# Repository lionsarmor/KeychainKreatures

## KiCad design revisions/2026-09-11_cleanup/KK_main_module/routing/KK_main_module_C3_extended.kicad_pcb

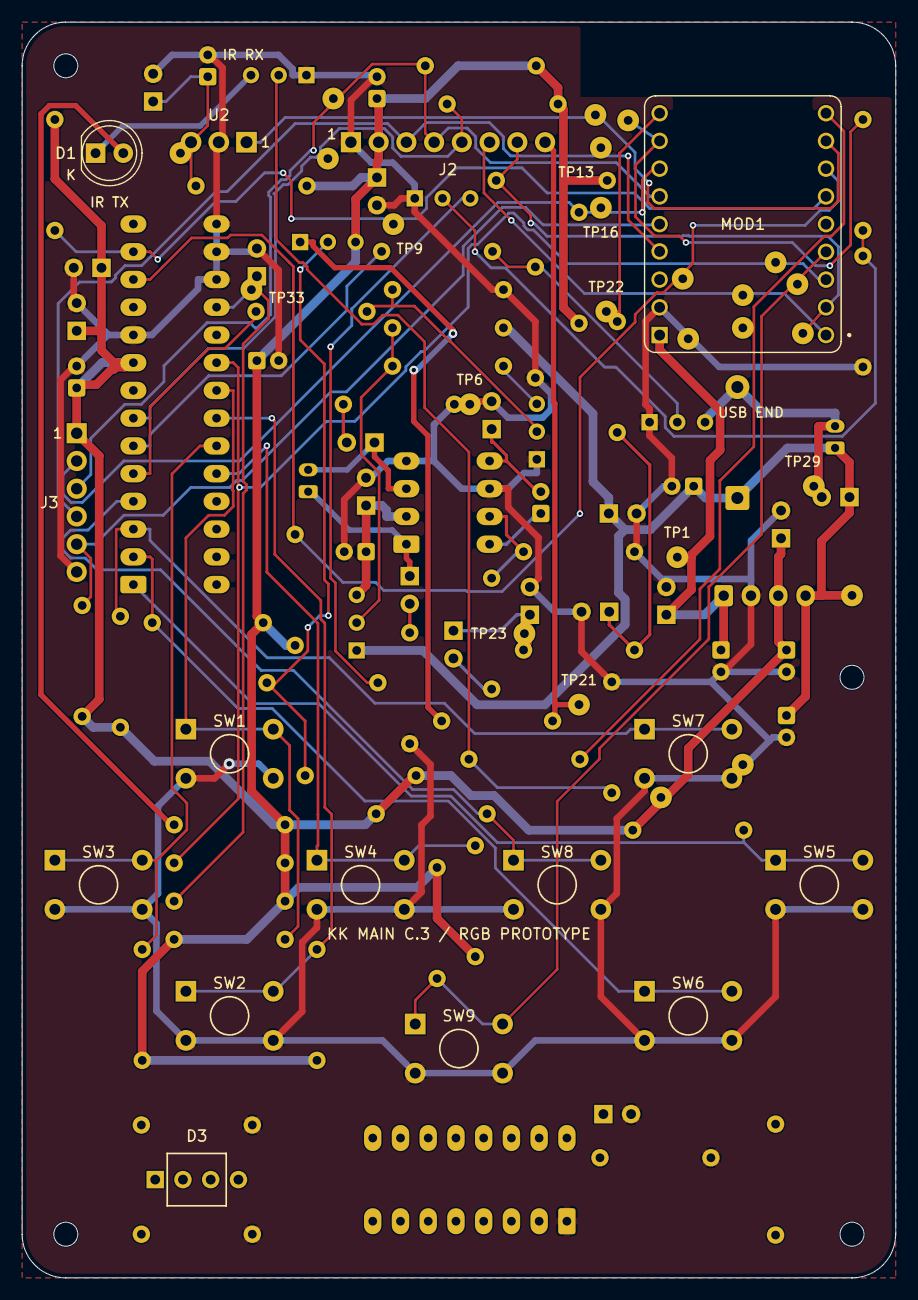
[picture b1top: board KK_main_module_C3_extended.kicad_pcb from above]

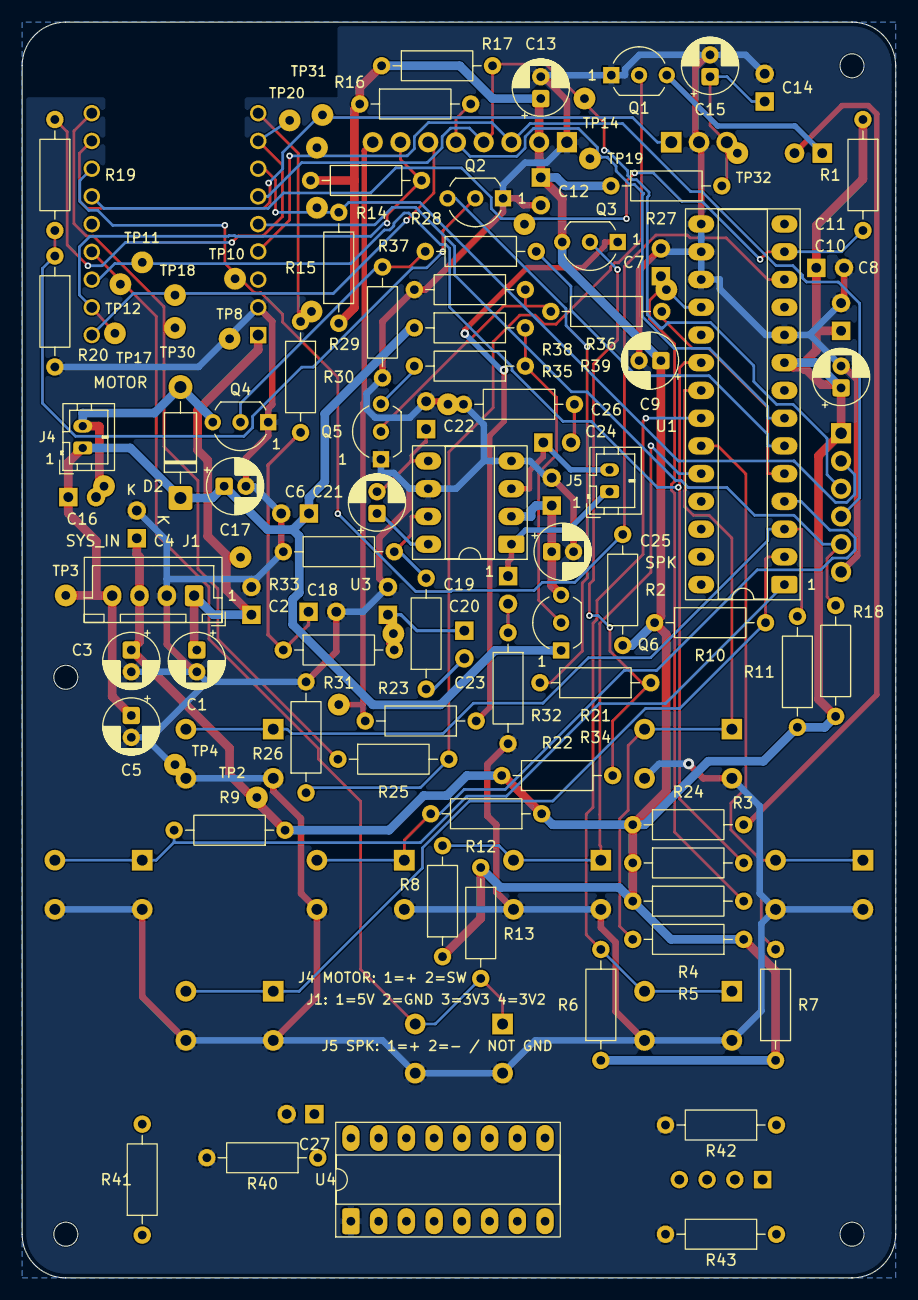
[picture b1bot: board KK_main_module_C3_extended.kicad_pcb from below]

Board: 2 copper layers, 80.0 x 115.0 mm, 127 parts (98 on the bottom side), 63 nets.

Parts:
C1, C3, C5, C13, C17, C25: 100u; Nichicon_UVR_D5_P2
C2, C4, C6, C7, C8, C10, C12, C14, C16, C23, C24, C26, C27: 100n; KEMET_C315_P2p54
C9, C11, C15, C21: 10u; Nichicon_UVR_D5_P2
C18, C19, C22: 10n; KEMET_C315_P2p54
C20: 1u; KEMET_C315_P2p54
D1: TSAL6200; TSAL6200_LED5
D2: 1N5819; 1N5819_DO41
D3: RGB mood / common anode; RGB_CA_5mm_LeadFormed
H1, H2, H3, H4: M2 2.2mm NPTH
J1: SYS_IN / JST-XH; JST_XH_B4B_4
J2: XIITIA TFT header; Sullins_PPTC081_LFB
J3: GODIYMODULES SD; Sullins_PPTC061_LFB
J4: LCM0827A3038F motor; JST_PH_B2B_2
J5: 8 ohm speaker; JST_PH_B2B_2
MOD1: ESP32-S3 SuperMini; ESP32-S3-SuperMini
Q1, Q2: KSP2222ABU; TO92_LeadFormed_P2p54
Q3: BC32725BU; TO92_LeadFormed_P2p54
Q4, Q5: TN0702N3-G; TO92_LeadFormed_P2p54
Q6: LP0701N3-G; TO92_LeadFormed_P2p54
R1, R2, R19: 4.7k; MFR25_10p16
R3, R4, R5, R6, R7, R8, R9, R10, R11, R12, R13, R14, R15, R16, R17, R18, R41: 10k; MFR25_10p16
R20, R22, R26, R29, R32, R37, R39, R42, R43: 100k; MFR25_10p16
R21: 220; MFR25_10p16
R23, R24, R27, R28: 100; MFR25_10p16
R25, R30, R31, R33, R36, R38: 1k; MFR25_10p16
R34, R35: 4.7; MFR25_10p16
R40: 1.8k; MFR25_10p16
SW1: UP; Adafruit3101_ABCD
SW2: DOWN; Adafruit3101_ABCD
SW3: LEFT; Adafruit3101_ABCD
SW4: RIGHT; Adafruit3101_ABCD
SW5: A; Adafruit3101_ABCD
SW6: B; Adafruit3101_ABCD
SW7: X; Adafruit3101_ABCD
SW8: Y; Adafruit3101_ABCD
SW9: FN; Adafruit3101_ABCD
TP1: 5V; Debug_PTH_2mm
TP2: 3V3; Debug_PTH_2mm
TP3: 3V2; Debug_PTH_2mm
TP4: GND-P; Debug_PTH_2mm
TP6: GND-A; Debug_PTH_2mm
TP8: GND-M; Debug_PTH_2mm
TP9: SDA; Debug_PTH_2mm
TP10: SCL; Debug_PTH_2mm
TP11: KEY-IRQ; Debug_PTH_2mm
TP12: FN; Debug_PTH_2mm
TP13: SCK; Debug_PTH_2mm
TP14: MOSI; Debug_PTH_2mm
TP16: SD-CS; Debug_PTH_2mm
TP17: TFT-CS; Debug_PTH_2mm
TP18: TFT-DC; Debug_PTH_2mm
TP19: TFT-RST; Debug_PTH_2mm
TP20: BL-PWM; Debug_PTH_2mm
TP21: BLK; Debug_PTH_2mm
TP22: AUD-PWM; Debug_PTH_2mm
TP23: AUD-LP2; Debug_PTH_2mm
TP29: MOT-RET; Debug_PTH_2mm
TP30: IR-TX; Debug_PTH_2mm
TP31: IR-RX; Debug_PTH_2mm
TP32: IR-V; Debug_PTH_2mm
TP33: IO-RST; Debug_PTH_2mm
U1: MCP23017-E/SP; ED281DT_DIP28_Socket
U2: TSOP38238; TSOP38238_Vertical
U3: TDA2822L-D08-T; ED08DT_DIP8_Socket
U4: TLC5916IN; ED16DT_DIP16_Socket

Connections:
/ACT_3V2: C5.1, C6.1, C16.1, C17.1, D2.1, J1.4, J4.1, Q6.1, R39.1, TP3.1
/AMP_EN: R36.1, U1.5
/AUDIO_PWM: MOD1.8, R30.1, TP22.1
/BL_PWM: MOD1.9, R19.1, TP20.1
/BUTTON_FN_N: MOD1.2, R13.2, SW9.A, SW9.B, TP12.1
/BUTTON_INT_N: MOD1.1, R3.2, TP11.1, U1.20
/GND: C1.2, C2.2, C3.2, C4.2, C5.2, C6.2, C7.2, C8.2, C9.2, C10.2, C11.2, C12.2, C13.2, C14.2, C15.2, C17.2, C18.2, C19.2, C22.2, C25.2, C26.2, C27.2, J1.2, J2.1, J3.6, MOD1.GND, Q1.1, Q2.1, Q4.1, Q5.1, R20.2, R26.2, R29.2, R33.2, R34.2, R35.2, R37.2, R40.2, R42.2, R43.2, SW1.C, SW1.D, SW2.C, SW2.D, SW3.C, SW3.D, SW4.C, SW4.D, SW5.C, SW5.D, SW6.C, SW6.D, SW7.C, SW7.D, SW8.C, SW8.D, SW9.C, SW9.D, TP4.1, TP6.1, TP8.1, U1.10, U1.15, U1.16, U1.17, U2.2, U3.4, U3.6, U4.1
/I2C_SCL: MOD1.5, R2.2, TP10.1, U1.12
/I2C_SDA: MOD1.4, R1.2, TP9.1, U1.13
/IR_RX: MOD1.6, TP31.1, U2.1
/IR_TX: MOD1.7, R25.1, TP30.1
/LOGIC_3V3: C3.1, C4.1, C8.1, C9.1, C10.1, C11.1, C12.1, C13.1, C27.1, J1.3, J2.2, J3.1, Q3.3, R1.1, R2.1, R3.1, R4.1, R5.1, R6.1, R7.1, R8.1, R9.1, R10.1, R11.1, R12.1, R13.1, R14.1, R15.1, R16.1, R17.1, R18.1, R22.1, R24.1, R27.1, R41.1, TP2.1, U1.9, U4.16
/MCU_5V: C1.1, C2.1, D3.2, J1.1, MOD1.5V, TP1.1
/MOTOR_EN: R28.1, U1.6
/RGB_CLK: R43.1, U1.26, U4.3
/RGB_DATA: R42.1, U1.25, U4.2
/RGB_LATCH: U1.27, U4.4
/RGB_OE_N: R41.2, U1.28, U4.13
/SD_CS: J3.2, MOD1.10, R15.2, TP16.1
/SPI_MISO: J3.5, MOD1.12, R18.2
/SPI_MOSI: J2.4, J3.3, MOD1.11, R17.2, TP14.1
/SPI_SCK: J2.3, J3.4, MOD1.13, TP13.1
/TFT_CS: J2.7, MOD1.RX, R14.2, TP17.1
/TFT_DC: J2.6, MOD1.TX, TP18.1
/TFT_RST_N: J2.5, R16.2, TP19.1, U1.7
unnamed: C18.1, R30.2, R31.1
unnamed: C19.1, C20.1, R31.2, TP23.1
unnamed: C20.2, R32.1
unnamed: C23.2, R34.1
unnamed: C24.2, R35.1
unnamed: D1.2, R24.2
unnamed: D1.1, Q1.3
unnamed: C16.2, D2.2, J4.2, Q4.3, TP29.1
unnamed: D3.3, U4.7
unnamed: D3.4, U4.6
unnamed: D3.1, U4.5
unnamed: J2.8, R23.2, TP21.1
unnamed: C23.1, J5.1, U3.1
unnamed: C24.1, J5.2, U3.3
unnamed: Q1.2, R25.2, R26.1
unnamed: Q2.2, R19.2, R20.1
unnamed: Q2.3, R21.2
unnamed: Q3.2, R21.1, R22.2
unnamed: Q3.1, R23.1
unnamed: Q4.2, R28.2, R29.1
unnamed: Q5.3, R38.2
unnamed: Q5.2, R36.2, R37.1
unnamed: C25.1, C26.1, Q6.3, U3.2
unnamed: Q6.2, R38.1, R39.2
unnamed: R5.2, SW1.A, SW1.B, U1.21
unnamed: R6.2, SW2.A, SW2.B, U1.22
unnamed: R7.2, SW3.A, SW3.B, U1.23
unnamed: R8.2, SW4.A, SW4.B, U1.24
unnamed: R9.2, SW5.A, SW5.B, U1.1
unnamed: R10.2, SW6.A, SW6.B, U1.2
unnamed: R11.2, SW7.A, SW7.B, U1.3
unnamed: R12.2, SW8.A, SW8.B, U1.4
unnamed: C7.1, R4.2, TP33.1, U1.18
unnamed: C14.1, C15.1, R27.2, TP32.1, U2.3
unnamed: R32.2, R33.1, U3.7
unnamed: C21.1, U3.8
unnamed: C21.2, C22.1, U3.5
unnamed: R40.1, U4.15

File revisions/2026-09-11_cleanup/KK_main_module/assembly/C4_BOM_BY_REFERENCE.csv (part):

Reference,Quantity,Value,MPN,Footprint,Side,Datasheet,Notes
C1,1,100u,UVR1C101MDD,KK_Main:Nichicon_UVR_D5_P2,back,https://www.nichicon.co.jp/english/series_items/catalog_pdf/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,
C2,1,100n,C315C104K5R5TA,KK_Main:KEMET_C315_P2p54,back,https://yageogroup.com/download/specsheet/C315C104K5R5TA,
C3,1,100u,UVR1C101MDD,KK_Main:Nichicon_UVR_D5_P2,back,https://www.nichicon.co.jp/english/series_items/catalog_pdf/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,
C4,1,100n,C315C104K5R5TA,KK_Main:KEMET_C315_P2p54,back,https://yageogroup.com/download/specsheet/C315C104K5R5TA,
C5,1,100u,UVR1C101MDD,KK_Main:Nichicon_UVR_D5_P2,back,https://www.nichicon.co.jp/english/series_items/catalog_pdf/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,
C6,1,100n,C315C104K5R5TA,KK_Main:KEMET_C315_P2p54,back,https://yageogroup.com/download/specsheet/C315C104K5R5TA,
C7,1,100n,C315C104K5R5TA,KK_Main:KEMET_C315_P2p54,back,https://yageogroup.com/download/specsheet/C315C104K5R5TA,
C8,1,100n,C315C104K5R5TA,KK_Main:KEMET_C315_P2p54,back,https://yageogroup.com/download/specsheet/C315C104K5R5TA,
C9,1,10u,UVR1C100MDD,KK_Main:Nichicon_UVR_D5_P2,back,https://www.nichicon.co.jp/english/series_items/catalog_pdf/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,
C10,1,100n,C315C104K5R5TA,KK_Main:KEMET_C315_P2p54,back,https://yageogroup.com/download/specsheet/C315C104K5R5TA,
C11,1,10u,UVR1C100MDD,KK_Main:Nichicon_UVR_D5_P2,back,https://www.nichicon.co.jp/english/series_items/catalog_pdf/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,
C12,1,100n,C315C104K5R5TA,KK_Main:KEMET_C315_P2p54,back,https://yageogroup.com/download/specsheet/C315C104K5R5TA,
C13,1,100u,UVR1C101MDD,KK_Main:Nichicon_UVR_D5_P2,back,https://www.nichicon.co.jp/english/series_items/catalog_pdf/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,
C14,1,100n,C315C104K5R5TA,KK_Main:KEMET_C315_P2p54,back,https://yageogroup.com/download/specsheet/C315C104K5R5TA,
C15,1,10u,UVR1C100MDD,KK_Main:Nichicon_UVR_D5_P2,back,https://www.nichicon.co.jp/english/series_items/catalog_pdf/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,
C16,1,100n,C315C104K5R5TA,KK_Main:KEMET_C315_P2p54,back,https://yageogroup.com/download/specsheet/C315C104K5R5TA,Suppression physically close to motor leads
C17,1,100u,UVR1C101MDD,KK_Main:Nichicon_UVR_D5_P2,back,https://www.nichicon.co.jp/english/series_items/catalog_pdf/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,
C18,1,10n,C315C103J1G5TA,KK_Main:KEMET_C315_P2p54,back,https://yageogroup.com/download/specsheet/C315C103J1G5TA,
C19,1,10n,C315C103J1G5TA,KK_Main:KEMET_C315_P2p54,back,https://yageogroup.com/download/specsheet/C315C103J1G5TA,
C20,1,1u,C315C105K5R5TA,KK_Main:KEMET_C315_P2p54,back,https://yageogroup.com/download/specsheet/C315C105K5R5TA,
C21,1,10u,UVR1C100MDD,KK_Main:Nichicon_UVR_D5_P2,back,https://www.nichicon.co.jp/english/series_items/catalog_pdf/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,
C22,1,10n,C315C103J1G5TA,KK_Main:KEMET_C315_P2p54,back,https://yageogroup.com/download/specsheet/C315C103J1G5TA,
C23,1,100n,C315C104K5R5TA,KK_Main:KEMET_C315_P2p54,back,https://yageogroup.com/download/specsheet/C315C104K5R5TA,
C24,1,100n,C315C104K5R5TA,KK_Main:KEMET_C315_P2p54,back,https://yageogroup.com/download/specsheet/C315C104K5R5TA,
C25,1,100u,UVR1C101MDD,KK_Main:Nichicon_UVR_D5_P2,back,https://www.nichicon.co.jp/english/series_items/catalog_pdf/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,
C26,1,100n,C315C104K5R5TA,KK_Main:KEMET_C315_P2p54,back,https://yageogroup.com/download/specsheet/C315C104K5R5TA,
D1,1,TSAL6200,TSAL6200,KK_Main:TSAL6200_LED5,front,https://www.vishay.com/docs/81010/tsal6200.pdf,
D2,1,1N5819,1N5819-E3/54,KK_Main:1N5819_DO41,back,https://www.vishay.com/docs/88525/1n5817.pdf,
J1,1,SYS_IN / JST-XH,B4B-XH-A(LF)(SN),KK_Main:JST_XH_B4B_4,back,https://www.jst-mfg.com/product/pdf/eng/eXH.pdf,4-rail-interface pins include ground; future supply must sequence rails together
J2,1,XIITIA TFT header,PPTC081LFBN-RC,KK_Main:Sullins_PPTC081_LFB,front,https://mm.digikey.com/Volume0/opasdata/d220001/medias/docus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,Display module B0DFWL25RB is a separate assembly item
J3,1,GODIYMODULES SD,PPTC061LFBN-RC,KK_Main:Sullins_PPTC061_LFB,front,https://mm.digikey.com/Volume0/opasdata/d220001/medias/docus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,SD module B0F82XWT4F is a separate assembly item
J4,1,LCM0827A3038F motor,B2B-PH-K-S(LF)(SN),KK_Main:JST_PH_B2B_2,back,https://www.jst-mfg.com/product/pdf/eng/ePH.pdf,C.4 top-entry JST-PH; not the former right-angle S2B. Mating PHR-2 remains unchanged.
J5,1,8 ohm speaker,B2B-PH-K-S(LF)(SN),KK_Main:JST_PH_B2B_2,back,https://www.jst-mfg.com/product/pdf/eng/ePH.pdf,C.4 top-entry JST-PH; not the former right-angle S2B. Mating PHR-2 remains unchanged.
MOD1,1,ESP32-S3 SuperMini,Teyleten B0D47HBFDY,KK_Main:ESP32-S3-SuperMini,front,https://www.espressif.com/sites/default/files/documentation/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,Carrier pad numbering/voltage path requires delivered-module qualification
Q1,1,KSP2222ABU,KSP2222ABU,KK_Main:TO92_LeadFormed_P2p54,back,https://www.onsemi.com/pdf/datasheet/ksp2222a-d.pdf,
Q2,1,KSP2222ABU,KSP2222ABU,KK_Main:TO92_LeadFormed_P2p54,back,https://www.onsemi.com/pdf/datasheet/ksp2222a-d.pdf,
Q3,1,BC32725BU,BC32725BU,KK_Main:TO92_LeadFormed_P2p54,back,https://www.onsemi.com/pub/Collateral/BC327-D.PDF,
Q4,1,TN0702N3-G,TN0702N3-G,KK_Main:TO92_LeadFormed_P2p54,back,https://ww1.microchip.com/downloads/en/DeviceDoc/TN0702-N-Ch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,
Q5,1,TN0702N3-G,TN0702N3-G,KK_Main:TO92_LeadFormed_P2p54,back,https://ww1.microchip.com/downloads/en/DeviceDoc/TN0702-N-Ch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,"C.2: NMOS gate driver, S-G-D pins 1-2-3."
Q6,1,LP0701N3-G,LP0701N3-G,KK_Main:TO92_LeadFormed_P2p54,back,https://ww1.microchip.com/downloads/en/DeviceDoc/LP0701-P-Ch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,C.2: PMOS S-G-D pins 1-2-3. Do not fit former BC327 here.
R1,1,4.7k,MFR-25FBF52-4K7,KK_Main:MFR25_10p16,back,https://yageogroup.com/content/Resource%20Library/Datasheet/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,
R2,1,4.7k,MFR-25FBF52-4K7,KK_Main:MFR25_10p16,back,https://yageogroup.com/content/Resource%20Library/Datasheet/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,
R3,1,10k,MFR-25FBF52-10K,KK_Main:MFR25_10p16,back,https://yageogroup.com/content/Resource%20Library/Datasheet/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,
R4,1,10k,MFR-25FBF52-10K,KK_Main:MFR25_10p16,back,https://yageogroup.com/content/Resource%20Library/Datasheet/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,
R5,1,10k,MFR-25FBF52-10K,KK_Main:MFR25_10p16,back,https://yageogroup.com/content/Resource%20Library/Datasheet/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,
R6,1,10k,MFR-25FBF52-10K,KK_Main:MFR25_10p16,back,https://yageogroup.com/content/Resource%20Library/Datasheet/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,
R7,1,10k,MFR-25FBF52-10K,KK_Main:MFR25_10p16,back,https://yageogroup.com/content/Resource%20Library/Datasheet/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,
R8,1,10k,MFR-25FBF52-10K,KK_Main:MFR25_10p16,back,https://yageogroup.com/content/Resource%20Library/Datasheet/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,
R9,1,10k,MFR-25FBF52-10K,KK_Main:MFR25_10p16,back,https://yageogroup.com/content/Resource%20Library/Datasheet/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,
R10,1,10k,MFR-25FBF52-10K,KK_Main:MFR25_10p16,back,https://yageogroup.com/content/Resource%20Library/Datasheet/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,
R11,1,10k,MFR-25FBF52-10K,KK_Main:MFR25_10p16,back,https://yageogroup.com/content/Resource%20Library/Datasheet/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,
R12,1,10k,MFR-25FBF52-10K,KK_Main:MFR25_10p16,back,https://yageogroup.com/content/Resource%20Library/Datasheet/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,
R13,1,10k,MFR-25FBF52-10K,KK_Main:MFR25_10p16,back,https://yageogroup.com/content/Resource%20Library/Datasheet/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,
R14,1,10k,MFR-25FBF52-10K,KK_Main:MFR25_10p16,back,https://yageogroup.com/content/Resource%20Library/Datasheet/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,
R15,1,10k,MFR-25FBF52-10K,KK_Main:MFR25_10p16,back,https://yageogroup.com/content/Resource%20Library/Datasheet/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,
R16,1,10k,MFR-25FBF52-10K,KK_Main:MFR25_10p16,back,https://yageogroup.com/content/Resource%20Library/Datasheet/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,
R17,1,10k,MFR-25FBF52-10K,KK_Main:MFR25_10p16,back,https://yageogroup.com/content/Resource%20Library/Datasheet/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,
R18,1,10k,MFR-25FBF52-10K,KK_Main:MFR25_10p16,back,https://yageogroup.com/content/Resource%20Library/Datasheet/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,
R19,1,4.7k,MFR-25FBF52-4K7,KK_Main:MFR25_10p16,back,https://yageogroup.com/content/Resource%20Library/Datasheet/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,
R20,1,100k,MFR-25FBF52-100K,KK_Main:MFR25_10p16,back,https://yageogroup.com/content/Resource%20Library/Datasheet/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,
R21,1,220,MFR-25FBF52-220R,KK_Main:MFR25_10p16,back,https://yageogroup.com/content/Resource%20Library/Datasheet/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,
R22,1,100k,MFR-25FBF52-100K,KK_Main:MFR25_10p16,back,https://yageogroup.com/content/Resource%20Library/Datasheet/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,
R23,1,100,MFR-25FBF52-100R,KK_Main:MFR25_10p16,back,https://yageogroup.com/content/Resource%20Library/Datasheet/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,Bring-up current limit; bright-screen qualification required
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
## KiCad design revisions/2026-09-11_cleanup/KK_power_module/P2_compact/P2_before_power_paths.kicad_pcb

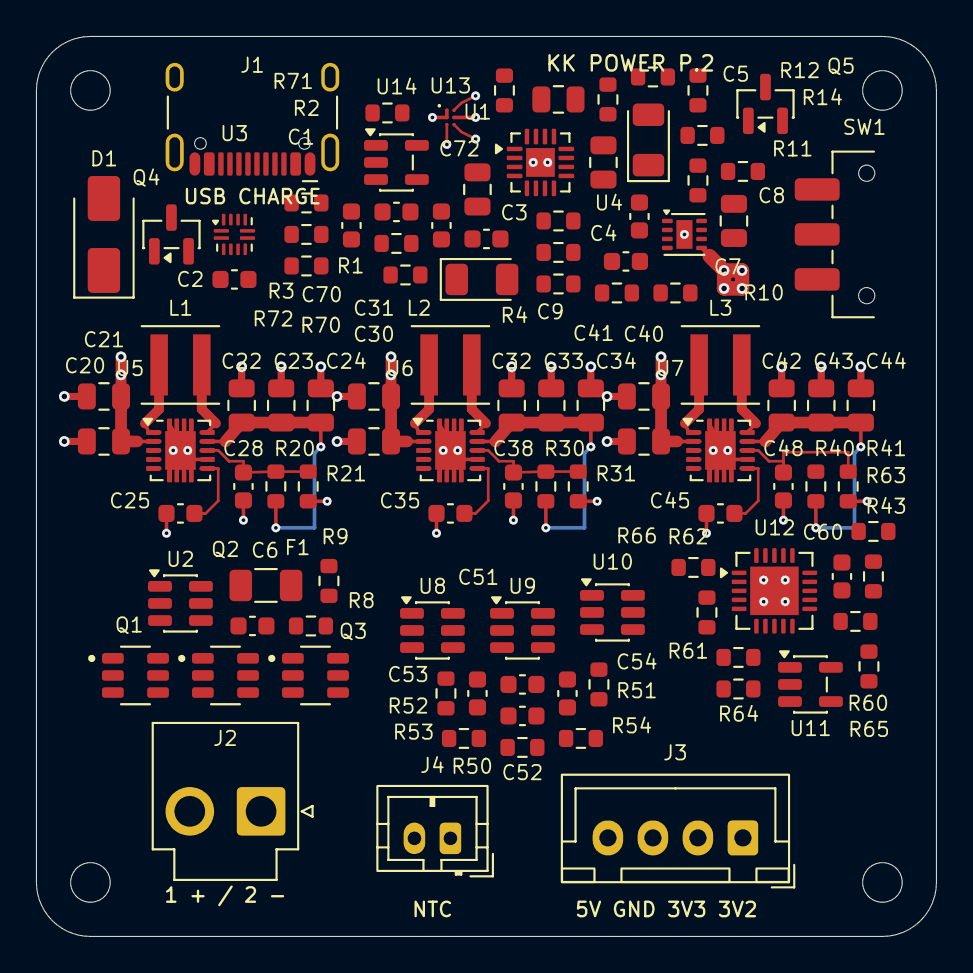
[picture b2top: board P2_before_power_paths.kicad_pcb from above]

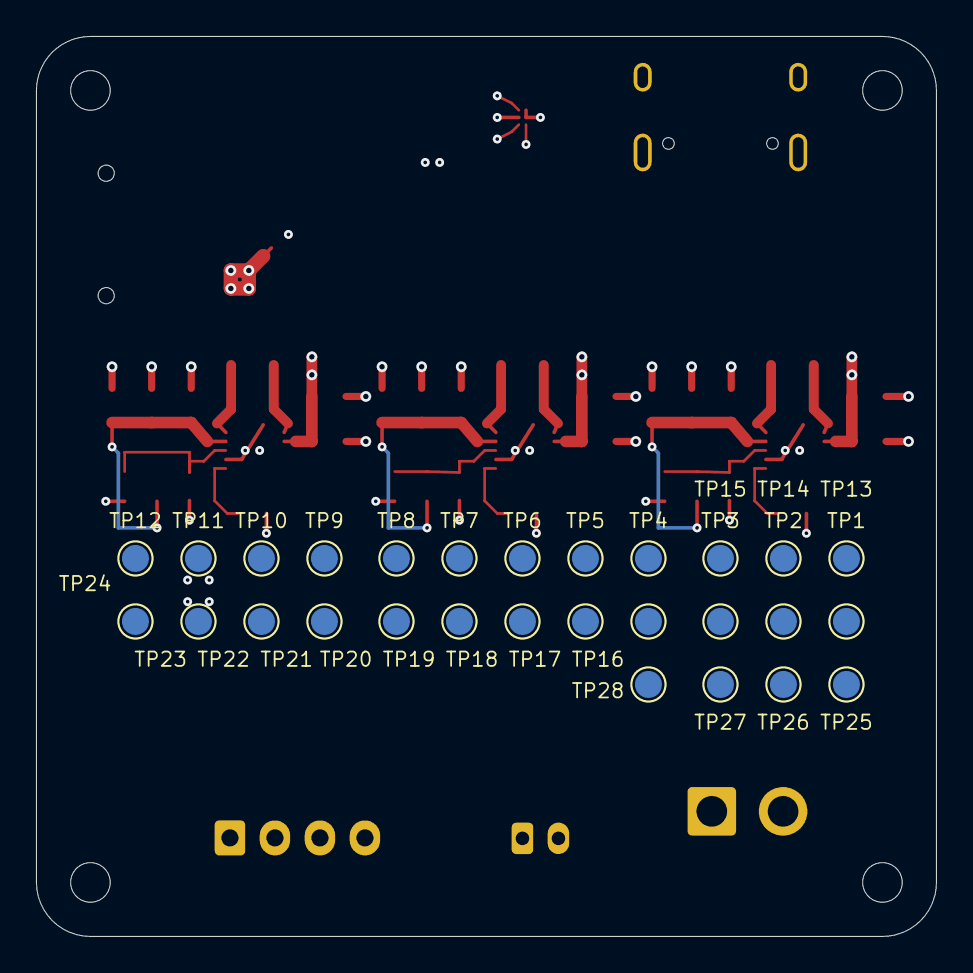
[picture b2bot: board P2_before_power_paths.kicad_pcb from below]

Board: 4 copper layers, 50.0 x 50.0 mm, 140 parts (28 on the bottom side), 66 nets.

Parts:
C1, C71, C72: 1u; C_0603_1608Metric
C2, C6, C9, C25, C35, C45, C51, C60, C70: 100n; C_0603_1608Metric
C3: 4.7u; C_0805_2012Metric
C4, C20, C21, C30, C31, C40, C41: 10u; C_0805_2012Metric
C5, C8, C22, C23, C24, C32, C33, C34, C42, C43, C44: 22u; C_0805_2012Metric
C7, C52, C53, C54: 10n; C_0603_1608Metric
C28, C38, C48: 10p; C_0603_1608Metric
D1: SMAJ5.0A; D_SMA
F1: 4A FAST; Fuse_1206_3216Metric
H1, H2, H3, H4: MountingHole_2.2mm_M2
J1: USB-C CHARGE ONLY; USB_C_HCTL
J2: 1S CELL / VH; JST_VH_B2P-VH_1x02_P3.96mm_Vertical
J3: C.5 SYS_IN / XH; JST_XH_B4B-XH-A_1x04_P2.50mm_Vertical
J4: BATTERY NTC; JST_PH_B2B-PH-K_1x02_P2.00mm_Vertical
L1, L2, L3: 1uH; L_Coilcraft_XxL4020
LED1: POWER GOOD; LED_1206_3216Metric
LED2: CHARGING; LED_1206_3216Metric
Q1, Q2, Q3: FS8205
Q4, Q5: AO3400A; SOT-23
R1: 887k; R_0603_1608Metric
R2, R6, R7: 4.7k; R_0603_1608Metric
R3, R14, R60: 10k; R_0603_1608Metric
R4: 2.94k; R_0603_1608Metric
R5: 1.3k; R_0603_1608Metric
R8: 470; R_0603_1608Metric
R9: 1k; R_0603_1608Metric
R10: 182k; R_0603_1608Metric
R11, R13, R31, R41, R51, R62, R64, R66, R72, R73: 100k; R_0603_1608Metric
R12: 620; R_0603_1608Metric
R20: 909k; R_0603_1608Metric
R21: 101k; R_0603_1608Metric
R30: 560k; R_0603_1608Metric
R40, R43: 270k; R_0603_1608Metric
R50: 470k; R_0603_1608Metric
R52, R53, R54: 100; R_0603_1608Metric
R61: 1060k; R_0603_1608Metric
R63: 665k; R_0603_1608Metric
R65: 649k; R_0603_1608Metric
R70: 19.2k; R_0603_1608Metric
R71: 634; R_0603_1608Metric
R74: 31.6k; R_0603_1608Metric
R75: 20k; R_0603_1608Metric
SW1: OFF / ON; SW_SPDT_CK_JS102011SAQN
TP1: VBUS; TestPoint_Pad_D1.5mm
TP2: VBAT; TestPoint_Pad_D1.5mm
TP3: BAT_NEG; TestPoint_Pad_D1.5mm
TP4: GND; TestPoint_Pad_D1.5mm
TP5: SYS_RAW; TestPoint_Pad_D1.5mm
TP6: SYS_SW; TestPoint_Pad_D1.5mm
TP7: RUN_CTL; TestPoint_Pad_D1.5mm
TP8: EF_UVLO; TestPoint_Pad_D1.5mm
TP9: EF_ILIM; TestPoint_Pad_D1.5mm
TP10: EF_FAULT_N; TestPoint_Pad_D1.5mm
TP11: PG_ALL; TestPoint_Pad_D1.5mm
TP12: RAILS_EN; TestPoint_Pad_D1.5mm
TP13: REG_5V; TestPoint_Pad_D1.5mm
TP14: REG_3V3; TestPoint_Pad_D1.5mm
TP15: REG_3V2; TestPoint_Pad_D1.5mm
TP16: MCU_5V; TestPoint_Pad_D1.5mm
TP17: LOGIC_3V3; TestPoint_Pad_D1.5mm
TP18: ACT_3V2; TestPoint_Pad_D1.5mm
TP19: NTC; TestPoint_Pad_D1.5mm
TP20: CC_DEFAULT_N; TestPoint_Pad_D1.5mm
TP21: USB_HIGH_CURRENT; TestPoint_Pad_D1.5mm
TP22: USB_CHG; TestPoint_Pad_D1.5mm
TP23: USB_PORT_ILIM; TestPoint_Pad_D1.5mm
TP24: USB_LIMIT_FAULT_N; TestPoint_Pad_D1.5mm
TP25: CC_3V3; TestPoint_Pad_D1.5mm
TP26: PGOOD_N; TestPoint_Pad_D1.5mm
TP27: CHARGE_N; TestPoint_Pad_D1.5mm
TP28: VOLTAGES_OK; TestPoint_Pad_D1.5mm
U1: BQ24075TRGTR; VQFN-16-1EP_3x3mm_P0.5mm_EP1.6x1.6mm
U2: DW01A / H&M; SOT-23-6
U3: TUSB320LAIRWBR; Texas_X2QFN-12_1.6x1.6mm_P0.4mm
U4: TPS259530DSGR; Texas_DSG0008A_WSON-8-1EP_2x2mm_P0.5mm_EP0.9x1.6mm
U5, U6, U7: TPS63060DSCR; Texas_S-PWSON-N10
U8, U9, U10: TPS22918DBVR; SOT-23-6
U11: SN74AUP1G17DBVR; SOT-23-5
U12: TPS386000RGPR; Texas_RGP0020D_VQFN-20-1EP_4x4mm_P0.5mm_EP2.7x2.7mm
U13: TPS22950YBHR; TPS22950_YBH
U14: TLV75533PDBVR; SOT-23-5

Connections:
/ACT_3V2: J3.4, R54.1, TP18.1, U10.6
/BAT_NEG: C6.2, J2.2, Q1.1, Q2.1, Q3.1, TP3.1, U2.6
/CC1: J1.A5, U3.1
/CC2: J1.B5, U3.2
/CC_3V3: C2.1, C72.1, R2.1, R3.1, TP25.1, U3.12, U14.5
/CC_DEFAULT_N: Q4.1, R2.2, TP20.1, U3.7
/CELL_PLUS: F1.1, J2.1
/CHARGE_N: R7.2, TP27.1, U1.9
/CHG_ILIM: R5.1, U1.12
/CHG_ISET: R4.1, U1.16
/DRAIN_COMMON: Q1.2, Q1.5, Q2.2, Q2.5, Q3.2, Q3.5
/EF_FAULT_N: R13.2, TP10.1, U4.6
/EF_ILIM: R12.1, TP9.1, U4.7
/EF_SLEW: C7.1, U4.1
/EF_UVLO: R10.2, R11.1, TP8.1, U4.2
/GND: C1.2, C2.2, C3.2, C4.2, C5.2, C7.2, C8.2, C9.2, C20.2, C21.2, C22.2, C23.2, C24.2, C25.2, C28.2, C30.2, C31.2, C32.2, C33.2, C34.2, C35.2, C38.2, C40.2, C41.2, C42.2, C43.2, C44.2, C45.2, C48.2, C51.2, C52.2, C53.2, C54.2, C60.2, C70.2, C71.2, C72.2, D1.2, J1.A1, J1.A12, J1.B1, J1.B12, J1.S1, J3.2, J4.2, Q1.3, Q2.3, Q3.3, Q4.2, Q5.2, R4.2, R5.2, R9.1, R11.2, R12.2, R21.2, R31.2, R41.2, R51.2, R62.2, R64.2, R66.2, R70.2, R72.2, R75.2, SW1.1, TP4.1, U1.4, U1.6, U1.8, U1.15, U1.17, U3.3, U3.10, U3.11, U4.8, U4.9, U5.7, U5.11, U6.7, U6.11, U7.7, U7.11, U8.2, U9.2, U10.2, U11.3, U12.6, U12.11, U12.12, U12.20, U12.21, U13.C1, U14.2
/LED1_K: LED1.1, R6.1
/LED2_K: LED2.1, R7.1
/LOGIC_3V3: J3.3, R53.1, TP17.1, U9.6
/MCU_5V: J3.1, R52.1, TP16.1, U8.6
/NTC: J4.1, R74.2, R75.1, TP19.1, U1.1
/OC: Q1.4, Q2.4, Q3.4, U2.3
/OD: Q1.6, Q2.6, Q3.6, U2.1
/PGOOD_N: R6.2, TP26.1, U1.7
/PG_ALL: R50.2, TP11.1, U5.5, U6.5, U7.5
/PROTECT_CS: R9.2, U2.2
/PROTECT_VCC: C6.1, R8.2, U2.5
/RAILS_EN: R51.1, TP12.1, U8.3, U9.3, U10.3, U11.4
/REG_3V2: C42.1, C43.1, C44.1, R40.1, R65.1, TP15.1, U7.9, U10.1
/REG_3V3: C32.1, C33.1, C34.1, C51.1, R30.1, R50.1, R60.1, R63.1, TP14.1, U6.9, U9.1, U11.5
/REG_5V: C22.1, C23.1, C24.1, R20.1, R61.1, TP13.1, U5.9, U8.1
/REG_ENABLE: R14.2, U5.3, U5.4, U6.3, U6.4, U7.3, U7.4
/RUN_CTL: R10.1, R14.1, SW1.2, TP7.1, U12.1
/SENSE_3V2: R65.2, R66.1, U12.8
/SENSE_3V3: R63.2, R64.1, U12.9
/SENSE_5V: R61.2, R62.1, U12.10
/SYS_RAW: C5.1, C9.1, C60.1, R13.1, SW1.3, TP5.1, U1.10, U1.11, U4.3, U4.4, U12.14
/SYS_SW: C8.1, C20.1, C21.1, C30.1, C31.1, C40.1, C41.1, TP6.1, U4.5, U5.2, U6.2, U7.2, U12.7
/U5_AUX: C25.1, U5.6
/U5_FB: C28.1, R20.2, R21.1, U5.8
/U5_L1: L1.1, U5.1
/U5_L2: L1.2, U5.10
/U6_AUX: C35.1, U6.6
/U6_FB: C38.1, R30.2, R31.1, U6.8
/U6_L1: L2.1, U6.1
/U6_L2: L2.2, U6.10
/U7_AUX: C45.1, U7.6
/U7_FB: C48.1, R41.1, R43.2, U7.8
/U7_FB_MID: R40.2, R43.1
/U7_L1: L3.1, U7.1
/U7_L2: L3.2, U7.10
/U8_CT: C52.1, U8.4
/U8_QOD: R52.2, U8.5
/U9_CT: C53.1, U9.4
/U9_QOD: R53.2, U9.5
/U10_CT: C54.1, U10.4
/U10_QOD: R54.2, U10.5
/USB_CHG: C3.1, C71.1, R74.1, TP22.1, U1.13, U13.B2
/USB_HIGH_CURRENT: Q4.3, Q5.1, R3.2, R72.1, TP21.1, U1.5
/USB_LIMIT_FAULT_N: R73.2, TP24.1, U13.A2
/USB_PORT_ILIM: R70.1, R71.1, TP23.1, U13.C2
/USB_PORT_ILIM_FAST: Q5.3, R71.2
/VBAT: C4.1, F1.2, R8.1, TP2.1, U1.2, U1.3
/VBUS: C1.1, C70.1, D1.1, J1.A4, J1.A9, J1.B4, J1.B9, LED1.2, LED2.2, R1.1, R73.1, TP1.1, U13.A1, U13.B1, U14.1, U14.3
/VBUS_DET: R1.2, U3.4
/VOLTAGES_OK: R60.2, TP28.1, U11.2, U12.15, U12.16, U12.17

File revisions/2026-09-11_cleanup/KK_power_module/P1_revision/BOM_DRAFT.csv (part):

Reference,Value,Candidate MPN - purchasing audit pending,Footprint,Group,Datasheet,Notes
J1,USB-C CHARGE ONLY,HC-TYPE-C-16P-01A,KK_Power:USB_C_HCTL,USB-C CHARGING ONLY,https://datasheet.lcsc.com/lcsc/2211161000_HCTL-HC-TYPE-C-16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,All USB D+/D- and SBU pins intentionally NC. Shield grounded.
U14,TLV75533PDBVR,TLV75533PDBVR,KK_Power:SOT-23-5,USB-C CHARGING ONLY,https://www.ti.com/lit/ds/symlink/tlv755p.pdf,"Dedicated USB-powered CC supply: TUSB320 VDD recommended maximum is 5V, so do not feed it raw USB. Not connected to main-board 3V3."
C72,1u,GRM188R71C105KA12D,KK_Power:C_0603_1608Metric,USB-C CHARGING ONLY,,Check effective capacitance at operating bias; 16V minimum for bulk.
U3,TUSB320LAIRWBR,TUSB320LAIRWBR,KK_Power:Texas_X2QFN-12_1.6x1.6mm_P0.4mm,USB-C CHARGING ONLY,https://www.ti.com/lit/ds/symlink/tusb320lai.pdf,Sink/GPIO mode; internal Rd. Pullups use the same regulated supply to avoid backpowering. Not a USB data controller.
R1,900k,RC0603FR07900KL,KK_Power:R_0603_1608Metric,USB-C CHARGING ONLY,,1% thick film
R2,4.7k,RC0603FR074K7L,KK_Power:R_0603_1608Metric,USB-C CHARGING ONLY,,1% thick film
Q4,AO3400A,AO3400A,KK_Power:SOT-23,USB-C CHARGING ONLY,https://www.aosmd.com/sites/default/files/res/datasheets/AO3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,Logic-level FET specified at 2.5V gate drive; clamps high-current request in default/unattached state.
R3,10k,RC0603FR0710KL,KK_Power:R_0603_1608Metric,USB-C CHARGING ONLY,,1% thick film
C1,1u,GRM188R71C105KA12D,KK_Power:C_0603_1608Metric,USB-C CHARGING ONLY,,Check effective capacitance at operating bias; 16V minimum for bulk.
C2,100n,GRM188R71C104KA01D,KK_Power:C_0603_1608Metric,USB-C CHARGING ONLY,,Check effective capacitance at operating bias; 16V minimum for bulk.
D1,SMAJ5.0A,SMAJ5.0A,KK_Power:D_SMA,USB-C CHARGING ONLY,,Unidirectional input TVS; pin 1 cathode.
U1,BQ24074RGTR,BQ24074RGTR,KK_Power:VQFN-16-1EP_3x3mm_P0.5mm_EP1.6x1.6mm,CELL CHARGER / POWER PATH,https://www.ti.com/lit/ds/symlink/bq24074.pdf,"Up to ~300mA charging on capable USB-C. Legacy input is ~50mA nominal, so charging is slow with toy off. Default timer/termination; EP solder required."
R4,3k,RC0603FR073KL,KK_Power:R_0603_1608Metric,CELL CHARGER / POWER PATH,,1% thick film
R5,1.3k,RC0603FR071K3L,KK_Power:R_0603_1608Metric,CELL CHARGER / POWER PATH,,1% thick film
C3,4.7u,GRM21BR71C475KA73L,KK_Power:C_0805_2012Metric,CELL CHARGER / POWER PATH,,Check effective capacitance at operating bias; 16V minimum for bulk.
C4,10u,GRM21BR61C106KE15L,KK_Power:C_0805_2012Metric,CELL CHARGER / POWER PATH,,Check effective capacitance at operating bias; 16V minimum for bulk.
C5,22u,GRM21BR61C226ME44L,KK_Power:C_0805_2012Metric,CELL CHARGER / POWER PATH,,Check effective capacitance at operating bias; 16V minimum for bulk.
J4,BATTERY NTC,B2B-PH-K-S(LF)(SN),KK_Power:JST_PH_B2B-PH-K_1x02_P2.00mm_Vertical,CELL CHARGER / POWER PATH,,10k NTC thermally bonded to cell. No fitted NO_NTC bypass.
LED1,POWER GOOD,APT3216LZGCK,KK_Power:LED_1206_3216Metric,CELL CHARGER / POWER PATH,,
R6,4.7k,RC0603FR074K7L,KK_Power:R_0603_1608Metric,CELL CHARGER / POWER PATH,,1% thick film
LED2,CHARGING,APT3216SURCK,KK_Power:LED_1206_3216Metric,CELL CHARGER / POWER PATH,,
R7,4.7k,RC0603FR074K7L,KK_Power:R_0603_1608Metric,CELL CHARGER / POWER PATH,,1% thick film
J2,1S CELL / VH,B2P-VH(LF)(SN),KK_Power:JST_VH_B2P-VH_1x02_P3.96mm_Vertical,CELL PROTECTION / FUSE,,Higher-current polarity-controlled cell harness. Requires a cell rated at least 4A continuous; not interchangeable with old PH or main-board XH harnesses.
F1,4A FAST,0451004.MRL,KK_Power:Fuse_1206_3216Metric,CELL PROTECTION / FUSE,,Secondary fault fuse; not a substitute for cell protection. Cell and fuse I-squared-t coordination still required.
U2,DW01A / H&M,DW01A,KK_Power:SOT-23-6,CELL PROTECTION / FUSE,https://hmsemi.com/downfile/DW01A.PDF,"H&M Semiconductor DW01A per linked manufacturer sheet. No generic substitutions. Parallel-FET trip thresholds, cell limits and fuse coordination remain release holds."
Q1,FS8205,FS8205,KK_Power:FS8205,CELL PROTECTION / FUSE,https://www.ic-fortune.com/upload/Download/FS8205-DS-19_EN.pdf,Three parallel matched dual-MOSFET banks. Must qualify current sharing and trip thresholds.
Q2,FS8205,FS8205,KK_Power:FS8205,CELL PROTECTION / FUSE,https://www.ic-fortune.com/upload/Download/FS8205-DS-19_EN.pdf,Three parallel matched dual-MOSFET banks. Must qualify current sharing and trip thresholds.
Q3,FS8205,FS8205,KK_Power:FS8205,CELL PROTECTION / FUSE,https://www.ic-fortune.com/upload/Download/FS8205-DS-19_EN.pdf,Three parallel matched dual-MOSFET banks. Must qualify current sharing and trip thresholds.
R8,470,RC0603FR07470RL,KK_Power:R_0603_1608Metric,CELL PROTECTION / FUSE,,1% thick film
R9,1k,RC0603FR071KL,KK_Power:R_0603_1608Metric,CELL PROTECTION / FUSE,,1% thick film
C6,100n,GRM188R71C104KA01D,KK_Power:C_0603_1608Metric,CELL PROTECTION / FUSE,,Check effective capacitance at operating bias; 16V minimum for bulk.
SW1,OFF / ON,JS102011SAQN,KK_Power:SW_SPDT_CK_JS102011SAQN,SYSTEM SWITCH / INRUSH / UVLO,https://www.ckswitches.com/media/1422/js.pdf,Signal-level switch only; charging remains on when toy off.
U4,TPS259530DSGR,TPS259530DSGR,KK_Power:Texas_DSG0008A_WSON-8-1EP_2x2mm_P0.5mm_EP0.9x1.6mm,SYSTEM SWITCH / INRUSH / UVLO,https://www.ti.com/lit/ds/symlink/tps2595.pdf,Latch-off on thermal fault; cycle switch to recover.
R10,182k,RT0603BRD07182KL,KK_Power:R_0603_1608Metric,SYSTEM SWITCH / INRUSH / UVLO,,0.1% thin film
R11,100k,RT0603BRD07100KL,KK_Power:R_0603_1608Metric,SYSTEM SWITCH / INRUSH / UVLO,,0.1% thin film
R12,620,RC0603FR07620RL,KK_Power:R_0603_1608Metric,SYSTEM SWITCH / INRUSH / UVLO,,1% thick film
C7,10n,GRM188R71H103KA01D,KK_Power:C_0603_1608Metric,SYSTEM SWITCH / INRUSH / UVLO,,Check effective capacitance at operating bias; 16V minimum for bulk.
C8,22u,GRM21BR61C226ME44L,KK_Power:C_0805_2012Metric,SYSTEM SWITCH / INRUSH / UVLO,,Check effective capacitance at operating bias; 16V minimum for bulk.
C9,100n,GRM188R71C104KA01D,KK_Power:C_0603_1608Metric,SYSTEM SWITCH / INRUSH / UVLO,,Check effective capacitance at operating bias; 16V minimum for bulk.
R13,100k,RC0603FR07100KL,KK_Power:R_0603_1608Metric,SYSTEM SWITCH / INRUSH / UVLO,,1% thick film
R14,10k,RC0603FR0710KL,KK_Power:R_0603_1608Metric,SYSTEM SWITCH / INRUSH / UVLO,,1% thick film
U5,TPS63060DSCR,TPS63060DSCR,KK_Power:Texas_S-PWSON-N10_ThermalVias,5 V BUCK-BOOST,https://www.ti.com/lit/ds/symlink/tps63060.pdf,Forced PWM for controlled rail accuracy/ripple. PG shared open-drain.
L1,1uH,XFL4020-102MEC,KK_Power:L_Coilcraft_XxL4020,5 V BUCK-BOOST,https://www.coilcraft.com/getmedia/50632d43-da1b-4cdb-8ab4-3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,"TI-recommended family; 5.1A Isat at 20% loss, manufacturer limits apply."
C20,10u,GRM21BR61C106KE15L,KK_Power:C_0805_2012Metric,5 V BUCK-BOOST,,Check effective capacitance at operating bias; 16V minimum for bulk.
C21,10u,GRM21BR61C106KE15L,KK_Power:C_0805_2012Metric,5 V BUCK-BOOST,,Check effective capacitance at operating bias; 16V minimum for bulk.
C22,22u,GRM21BR61C226ME44L,KK_Power:C_0805_2012Metric,5 V BUCK-BOOST,,Check effective capacitance at operating bias; 16V minimum for bulk.
C23,22u,GRM21BR61C226ME44L,KK_Power:C_0805_2012Metric,5 V BUCK-BOOST,,Check effective capacitance at operating bias; 16V minimum for bulk.
C24,22u,GRM21BR61C226ME44L,KK_Power:C_0805_2012Metric,5 V BUCK-BOOST,,Check effective capacitance at operating bias; 16V minimum for bulk.
C25,100n,GRM188R71C104KA01D,KK_Power:C_0603_1608Metric,5 V BUCK-BOOST,,Check effective capacitance at operating bias; 16V minimum for bulk.
C26,100n,GRM188R71C104KA01D,KK_Power:C_0603_1608Metric,5 V BUCK-BOOST,,Check effective capacitance at operating bias; 16V minimum for bulk.
C27,100n,GRM188R71C104KA01D,KK_Power:C_0603_1608Metric,5 V BUCK-BOOST,,Check effective capacitance at operating bias; 16V minimum for bulk.
R20,909k,RT0603BRD07909KL,KK_Power:R_0603_1608Metric,5 V BUCK-BOOST,,0.1% thin film
R21,101k,RT0603BRD07101KL,KK_Power:R_0603_1608Metric,5 V BUCK-BOOST,,0.1% thin film
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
